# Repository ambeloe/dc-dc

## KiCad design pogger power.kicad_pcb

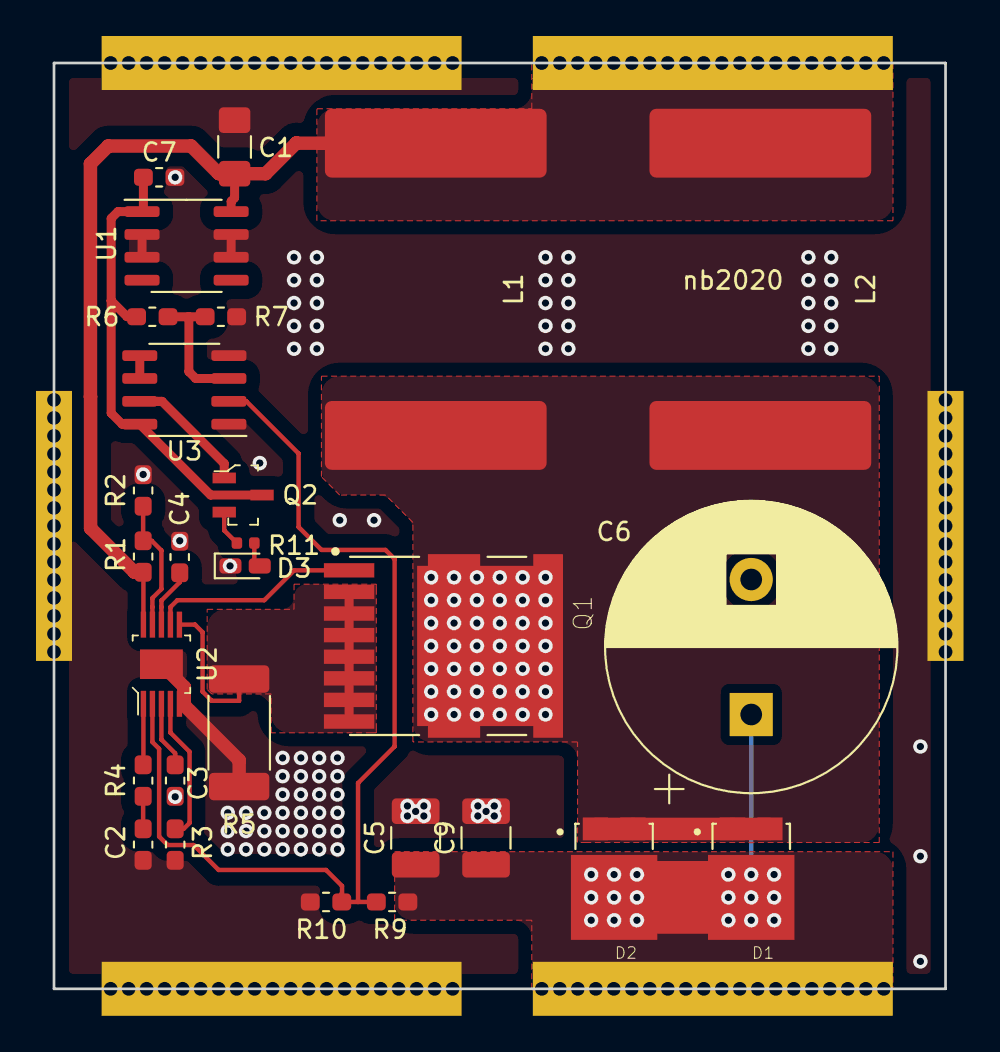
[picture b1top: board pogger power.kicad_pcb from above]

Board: 2 copper layers, 49.5 x 51.4 mm, 34 parts (0 on the bottom side), 19 nets.

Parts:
C1: 10uF; C_1206_3216Metric_Pad1.42x1.75mm_HandSolder
C2: 6.8nF; C_0603_1608Metric_Pad1.05x0.95mm_HandSolder
C3: 80nF; C_0603_1608Metric_Pad1.05x0.95mm_HandSolder
C4, C7: 4.7uF; C_0603_1608Metric_Pad1.05x0.95mm_HandSolder
C5, C9: 10uF; C_1210_3225Metric_Pad1.42x2.65mm_HandSolder
C6: 220uF; CP_Radial_D16.0mm_P7.50mm
D1, D2: D_AAK; to-277-3
D3: LED; LED_0603_1608Metric_Castellated
J1, J2, J3, J4: Conn_01x01_Female; castellated edge 20mm
J5, J6: Conn_01x01_Female; shortcastellated
L1, L2: 2.2uH; IHLP6767GZER2R2M01
Q1: FDBL86361-F085; MOSFET_FDBL86361-F085
Q2: BSS84; SOT-23-3
R1: 150k; R_0603_1608Metric_Pad1.05x0.95mm_HandSolder
R2, R7, R10: 10k; R_0603_1608Metric_Pad1.05x0.95mm_HandSolder
R3: 40k; R_0603_1608Metric_Pad1.05x0.95mm_HandSolder
R4, R6: 22k; R_0603_1608Metric_Pad1.05x0.95mm_HandSolder
R5: 800u; R_2512_6332Metric_Pad1.52x3.35mm_HandSolder
R9: 365k; R_0603_1608Metric_Pad1.05x0.95mm_HandSolder
R11: 150R; R_0402_1005Metric
U1: L78L05_SO8; SOIC-8_3.9x4.9mm_P1.27mm
U2: LT3757; MSOP-10-1EP_W3mm
U3: LM311; SOIC-8_3.9x4.9mm_P1.27mm

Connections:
+5V: C7.1, Q2.3, R6.1, U1.1, U3.8
FB: R9.2, R10.1, U2.2, U3.2
GND: C1.2, C2.2, C3.2, C4.2, C5.2, C6.2, C7.2, C9.2, D3.1, J2.1, J3.1, J5.1, J6.1, R2.2, R3.2, R5.2, R7.2, R10.2, U1.2, U1.3, U1.6, U1.7, U2.5, U2.11, U3.1, U3.4
unnamed: C2.1, R4.2
unnamed: C3.1, U2.3
unnamed: C4.1, U2.8
unnamed: D1.1, D1.2, D2.1, D2.2, L1.2, L2.2, Q1.9_1, Q1.9_2, Q1.9_3, Q1.9_4
unnamed: D3.2, R11.1
unnamed: Q1.1, U2.7
unnamed: Q1.2, Q1.3, Q1.4, Q1.5, Q1.6, Q1.7, Q1.8, R5.1, U2.6
unnamed: Q2.1, U3.7
unnamed: R1.2, R2.1, U2.9
unnamed: R3.1, U2.4
unnamed: R4.1, U2.1
unnamed: R6.2, R7.1, U3.3
unnamed: U3.5, U3.6
PWRGOOD: Q2.2, R11.2
VIN: C1.1, J1.1, L1.1, L2.1, R1.1, U1.8, U2.10
VOUT: C5.1, C6.1, C9.1, D1.3, D2.3, J4.1, R9.1

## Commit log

2020-07-10 added silkscreen labels
2020-07-11 fixed footprint of output ceramic caps
2020-07-25 added pdf schematic so it isnt cancer to look at
